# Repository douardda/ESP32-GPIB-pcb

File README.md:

# ESP32 based GPIB interface - Kicad design files

This is a simple GPIB interface design using an ESP32 board as main controller. It can
(optionally but highly recommanded) use a couple of driver ICs (SN75160 and SN75161/162).

The design consist in 2 boards coupled together: one with the IEEE488 connector and
driver ICs, and one with the Arduino or ESP32 board.

Doing so, the common GPIB board can be used with several Arduino/ESP32 boards.

3D view of the common IEEE488 board:

3D view of the interface board for the ESP32-S2-saola:

3D view of the interface board for the Arduini nano:

Interface using a generic ESP32 Devkit-c board:

This design is licensed under the 
[CC-BY-SA 4.0](https://creativecommons.org/licenses/by-sa/4.0/) license.

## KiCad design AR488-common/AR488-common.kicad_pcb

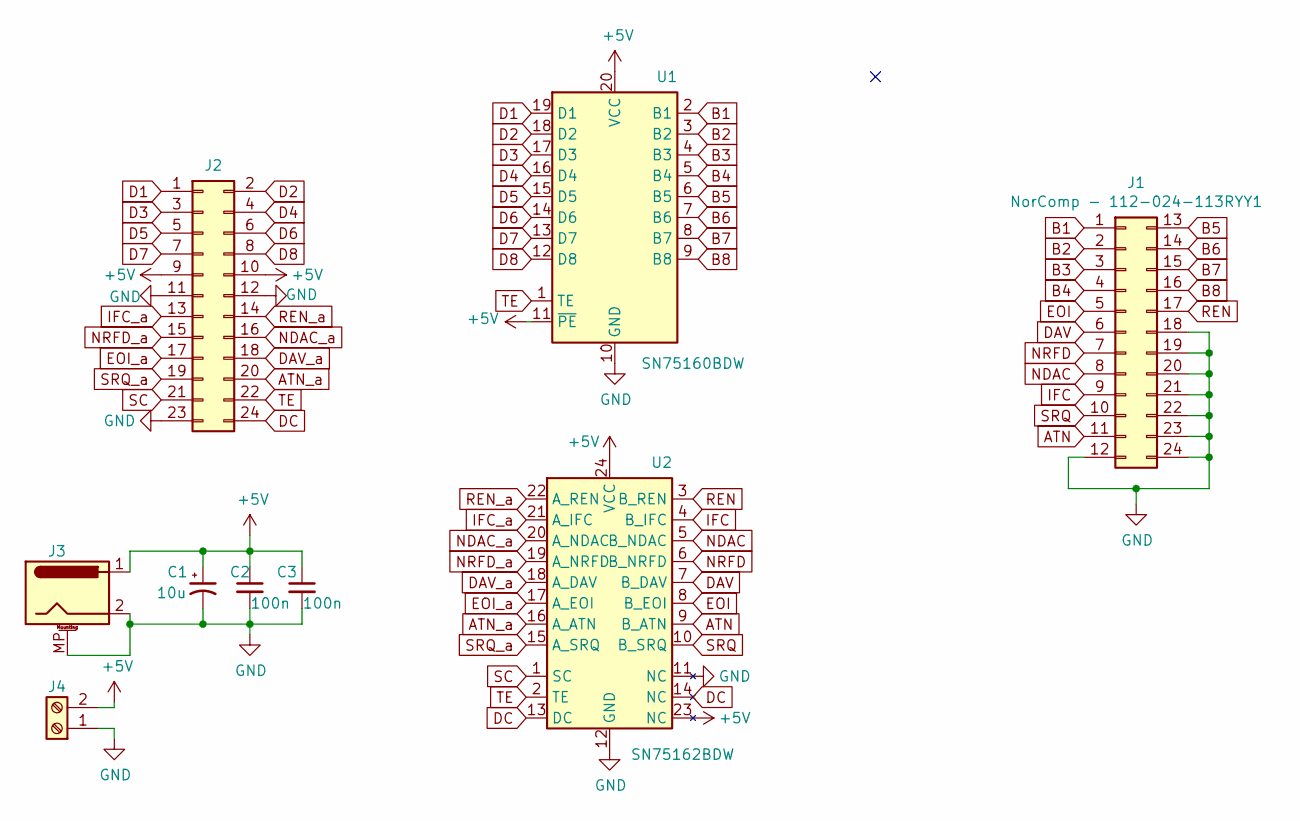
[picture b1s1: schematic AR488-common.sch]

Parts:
C1: 10u; CP_EIA-7132-20_AVX-U
C2, C3: 100n; C_1206_3216Metric
J1: NorComp - 112-024-113RYY1; CENTRONICS-24
J2: Conn_02x12_Odd_Even; PinSocket_2x12_P2.54mm_Vertical
J3: Barrel_Jack; BarrelJack_CUI_PJ-063AH_Horizontal
J4: Screw_Terminal_01x02; TerminalBlock_Altech_AK300-2_P5.00mm
U1: SN75160BDW; SOIC-20W_7.5x12.8mm_P1.27mm
U2: SN75162BDW; SOIC-24W_7.5x15.4mm_P1.27mm

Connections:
+5V: C1.1, C2.1, C3.1, J2.9, J2.10, J3.1, J4.2, U1.11 (~PE), U1.20 (VCC), U2.23 (NC), U2.24 (VCC)
ATN: J1.11, U2.9 (B_ATN)
ATN_a: J2.20, U2.16 (A_ATN)
B1: J1.1, U1.2 (B1)
B2: J1.2, U1.3 (B2)
B3: J1.3, U1.4 (B3)
B4: J1.4, U1.5 (B4)
B5: J1.13, U1.6 (B5)
B6: J1.14, U1.7 (B6)
B7: J1.15, U1.8 (B7)
B8: J1.16, U1.9 (B8)
D1: J2.1, U1.19 (D1)
D2: J2.2, U1.18 (D2)
D3: J2.3, U1.17 (D3)
D4: J2.4, U1.16 (D4)
D5: J2.5, U1.15 (D5)
D6: J2.6, U1.14 (D6)
D7: J2.7, U1.13 (D7)
D8: J2.8, U1.12 (D8)
DAV: J1.6, U2.7 (B_DAV)
DAV_a: J2.18, U2.18 (A_DAV)
DC: J2.24, U2.13 (DC), U2.14 (NC)
EOI: J1.5, U2.8 (B_EOI)
EOI_a: J2.17, U2.17 (A_EOI)
GND: C1.2, C2.2, C3.2, J1.12, J1.18, J1.19, J1.20, J1.21, J1.22, J1.23, J1.24, J2.11, J2.12, J2.23, J3.2, J3.MP (MountPin), J4.1, U1.10 (GND), U2.11 (NC), U2.12 (GND)
IFC: J1.9, U2.4 (B_IFC)
IFC_a: J2.13, U2.21 (A_IFC)
NDAC: J1.8, U2.5 (B_NDAC)
NDAC_a: J2.16, U2.20 (A_NDAC)
NRFD: J1.7, U2.6 (B_NRFD)
NRFD_a: J2.15, U2.19 (A_NRFD)
REN: J1.17, U2.3 (B_REN)
REN_a: J2.14, U2.22 (A_REN)
SC: J2.21, U2.1 (SC)
SRQ: J1.10, U2.10 (B_SRQ)
SRQ_a: J2.19, U2.15 (A_SRQ)
TE: J2.22, U1.1 (TE), U2.2 (TE)

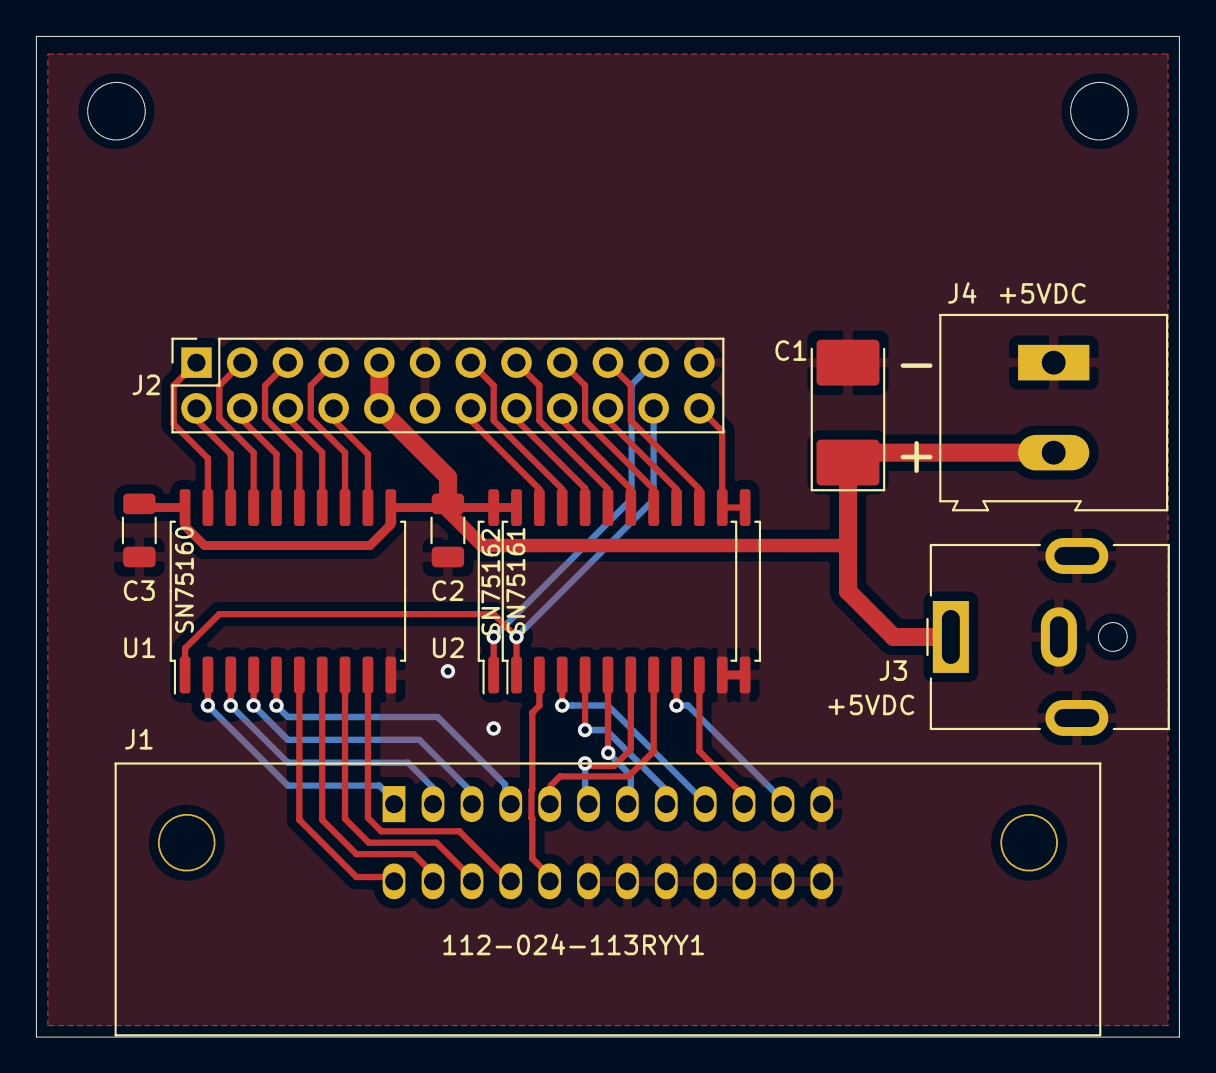
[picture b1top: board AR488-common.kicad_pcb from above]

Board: 2 copper layers, 63.5 x 55.6 mm, 9 parts (0 on the bottom side), 37 nets.

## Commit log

2021-10-30 First version of the GPIB/SN7616x board + esp32-saola daughter board
2021-10-30 Better pin assignment for the inter-PCB connector
2021-10-31 Finish the commons board + esp32 s2 soala + esp32 devkitc boards
2021-10-31 Add an arduino nano board
2021-11-14 Add a gitignore file
2022-03-12 Several minor fixes and adjustments in PCBs
2022-03-12 Add a quick README
2022-03-12 Typos in README and add a few pictures of an assembled interface
2022-05-14 Add the CC-BY-SA license info in the README file
2022-05-14 Use relative path for assets in the README file
2022-05-14 Add a LICENSE file
2022-06-18 Fix the ESP32-devkitc board
    - CMD was connected to GND
    - swap GPIO2 dn GPIO15 to fix boot issues

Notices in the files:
AR488-common/AR488-common.kicad_pcb:
CC BY-SA 3.0
README.md:
License: CC BY-SA 4.0
